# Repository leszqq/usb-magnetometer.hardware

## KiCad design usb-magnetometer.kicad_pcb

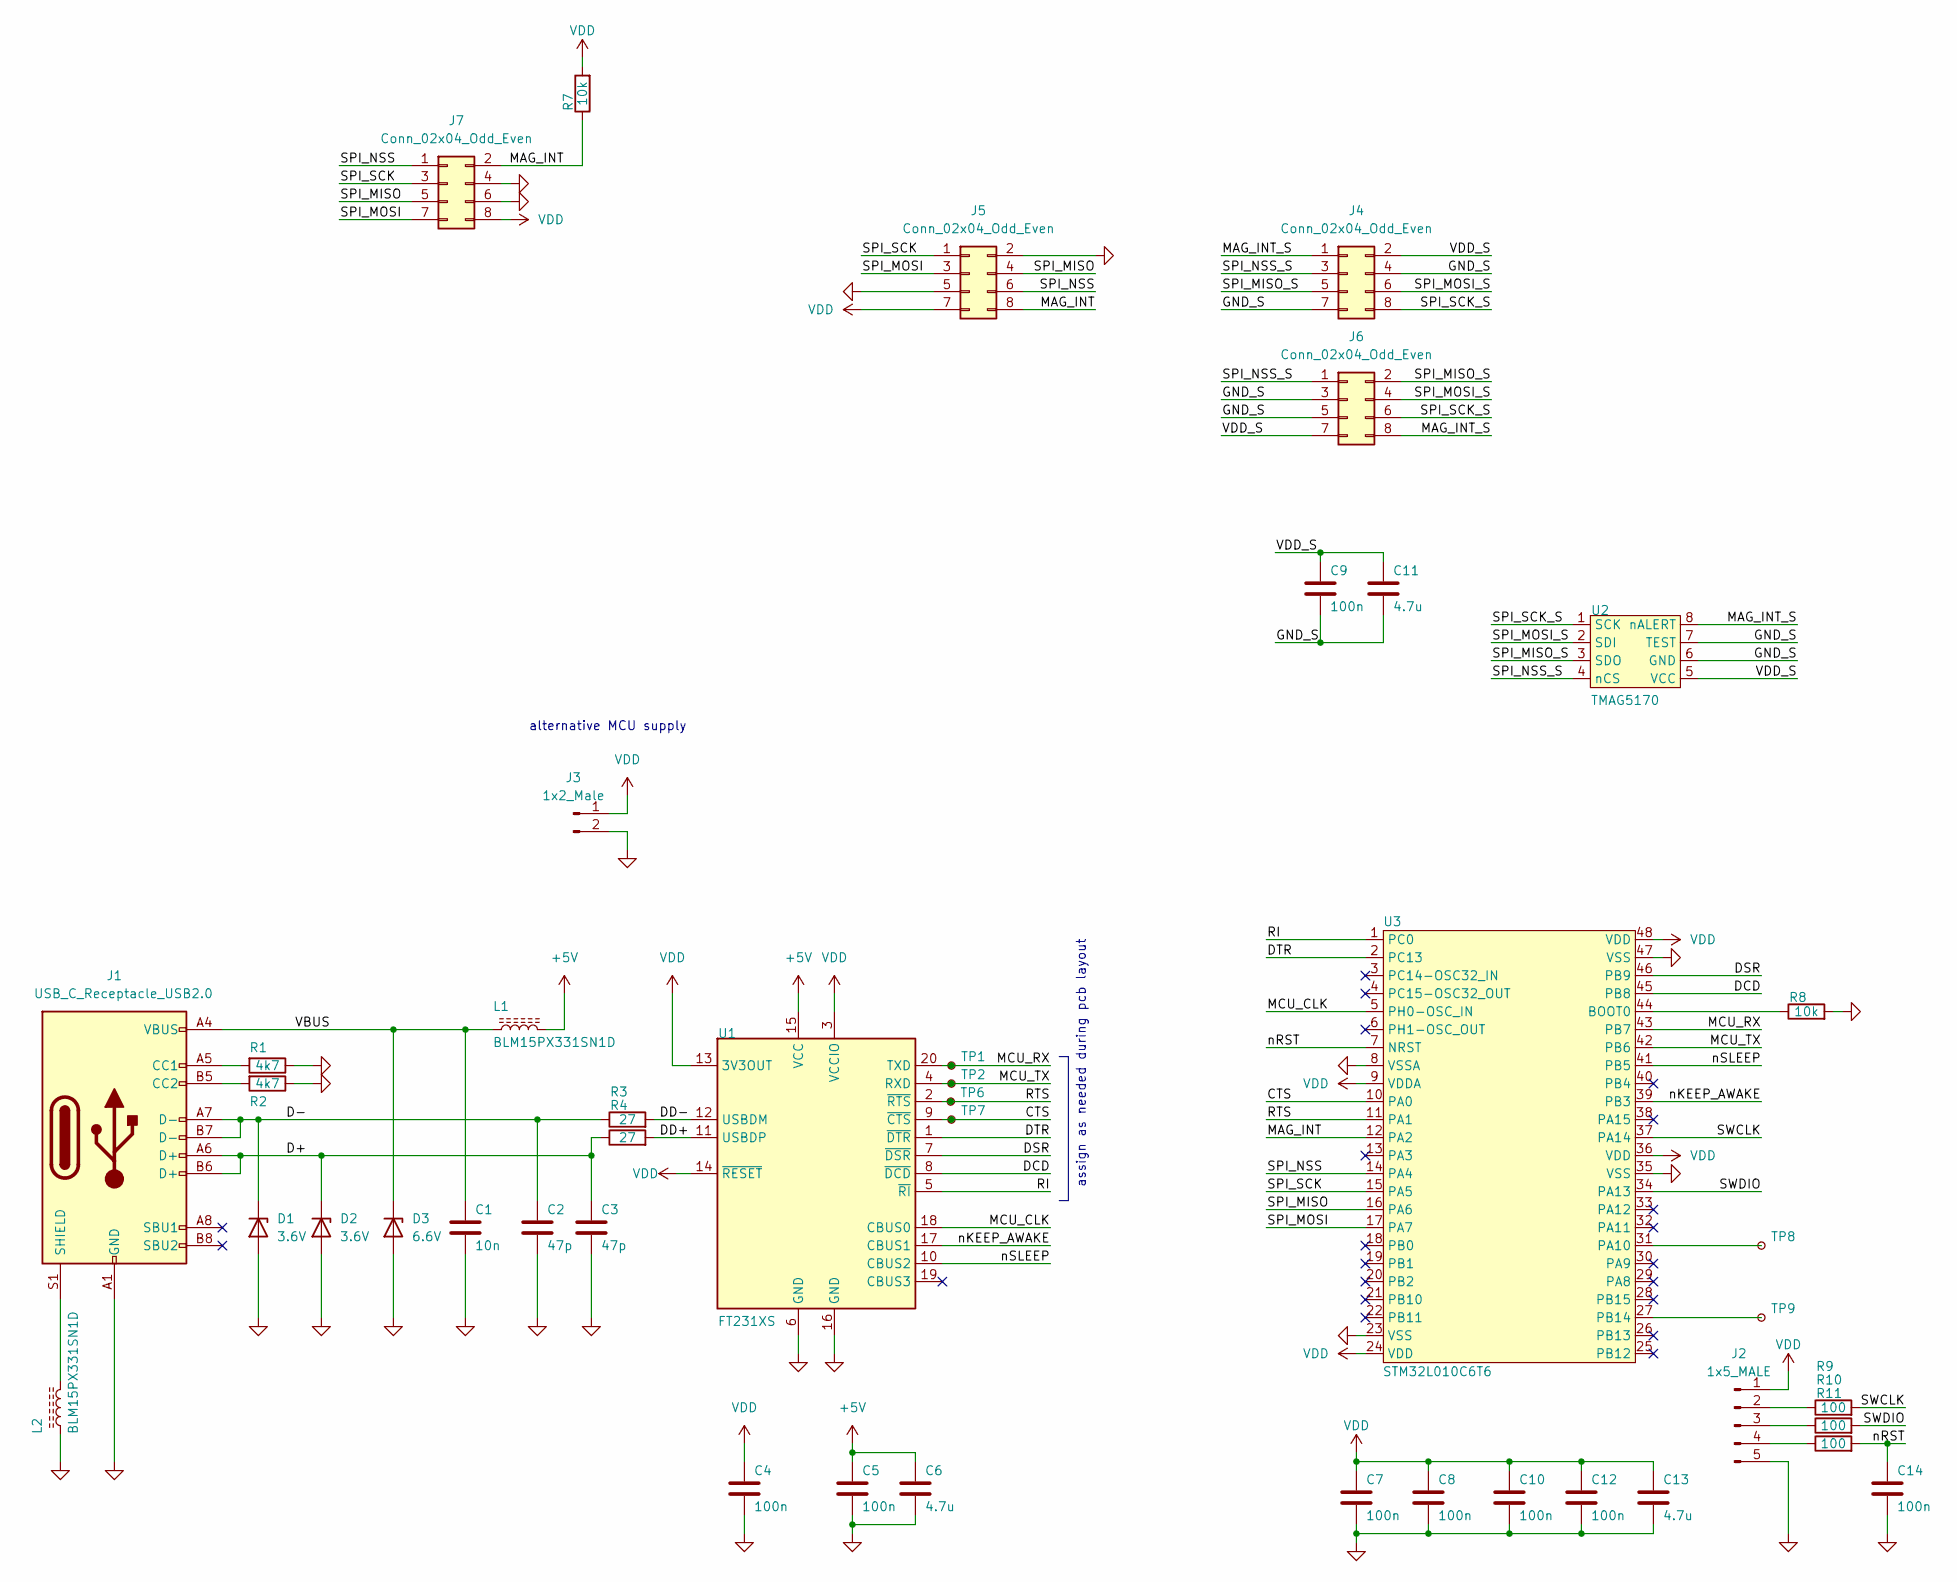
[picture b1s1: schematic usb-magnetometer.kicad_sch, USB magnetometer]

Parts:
C1: 10n; C_0402_1005Metric_Pad0.74x0.62mm_HandSolder; MPN VJ0402Y103JXQCW1BC
C2, C3: 47p; C_0402_1005Metric_Pad0.74x0.62mm_HandSolder; MPN CC0402JRNPO8BN470
C4, C5, C7, C8, C9, C10, C12, C14: 100n; C_0402_1005Metric_Pad0.74x0.62mm_HandSolder; MPN CL05A104KP5NNNC
C6, C11, C13: 4.7u; C_0402_1005Metric_Pad0.74x0.62mm_HandSolder; MPN CL05A475MP5NRNC
D1, D2: 3.6V; X1SON; MPN ESD321DPYR
D3: 6.6V; D_SOD-323_HandSoldering; MPN ESD3Z5V0
J1: USB_C_Receptacle_USB2.0; USB_C_Receptacle_JAE_DX07S016JA1R1500; MPN DX07S016JA1R1500
J2: 1x5_MALE; PinHeader_1x05_P2.54mm_Vertical; MPN *
J3: 1x2_Male; PinHeader_1x02_P2.54mm_Vertical; MPN *
J4, J5: Conn_02x04_Odd_Even; Hirose_FH12-8S-0.5SH_1x08-1MP_P0.50mm_Horizontal
J6, J7: Conn_02x04_Odd_Even; PinHeader_2x04_P1.00mm_Vertical
L1, L2: L_Ferrite; R_0402_1005Metric_Pad0.72x0.64mm_HandSolder; MPN BLM15PX331SN1D
R1, R2: 4k7; R_0402_1005Metric_Pad0.72x0.64mm_HandSolder; MPN RC0402JR-134K7L
R3, R4: 27; R_0402_1005Metric_Pad0.72x0.64mm_HandSolder; MPN RC0402JR-0727RL
R7, R8: 10k; R_0402_1005Metric_Pad0.72x0.64mm_HandSolder; MPN RC0402FR-0710KL
R9, R10, R11: 100; R_0402_1005Metric_Pad0.72x0.64mm_HandSolder; MPN RC0402FR-07100R
TP1, TP2, TP6, TP7, TP8, TP9: TestPoint_Small; TestPoint_Pad_D1.0mm
U1: FT231XS; SSOP-20_3.9x8.7mm_P0.635mm; MPN FT231XS-R
U2: TMAG5170; VSSOP-8_3.0x3.0mm_P0.65mm; MPN TMAG5170A1EDGKRQ1
U3: STM32L010C6T6; LQFP-48_7x7mm_P0.5mm; MPN STM32L010C6T6

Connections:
+5V: C5.1, C6.1, L1.2, U1.15 (VCC)
/CTS: TP7.1, U1.9 (~CTS), U3.10 (PA0)
/D+: C3.1, D2.1 (K), J1.A6 (D+), J1.B6 (D+), R4.1
/D-: C2.1, D1.1 (K), J1.A7 (D-), J1.B7 (D-), R3.1
/DCD: U1.8 (~DCD), U3.45 (PB8)
/DD+: R4.2, U1.11 (USBDP)
/DD-: R3.2, U1.12 (USBDM)
/DSR: U1.7 (~DSR), U3.46 (PB9)
/DTR: U1.1 (~DTR), U3.2 (PC13)
/GND_S: C9.2, C11.2, J4.4, J4.7, J6.3, J6.5, U2.6 (GND), U2.7 (TEST)
/MAG_INT: J5.8, J7.2, R7.1, U3.12 (PA2)
/MAG_INT_S: J4.1, J6.8, U2.8 (nALERT)
/MCU_CLK: U1.18 (CBUS0), U3.5 (PH0-OSC_IN)
/MCU_RX: TP1.1, U1.20 (TXD), U3.43 (PB7)
/MCU_TX: TP2.1, U1.4 (RXD), U3.42 (PB6)
/RI: U1.5 (~RI), U3.1 (PC0)
/RTS: TP6.1, U1.2 (~RTS), U3.11 (PA1)
/SPI_MISO: J5.4, J7.5, U3.16 (PA6)
/SPI_MISO_S: J4.5, J6.2, U2.3 (SDO)
/SPI_MOSI: J5.3, J7.7, U3.17 (PA7)
/SPI_MOSI_S: J4.6, J6.4, U2.2 (SDI)
/SPI_NSS: J5.6, J7.1, U3.14 (PA4)
/SPI_NSS_S: J4.3, J6.1, U2.4 (nCS)
/SPI_SCK: J5.1, J7.3, U3.15 (PA5)
/SPI_SCK_S: J4.8, J6.6, U2.1 (SCK)
/SWCLK: R9.2, U3.37 (PA14)
/SWDIO: R10.2, U3.34 (PA13)
/VBUS: C1.1, D3.1 (K), J1.A4 (VBUS), J1.A9 (VBUS), J1.B4 (VBUS), J1.B9 (VBUS), L1.1
/VDD_S: C9.1, C11.1, J4.2, J6.7, U2.5 (VCC)
/nKEEP_AWAKE: U1.17 (CBUS1), U3.39 (PB3)
/nRST: C14.1, R11.2, U3.7 (NRST)
/nSLEEP: U1.10 (CBUS2), U3.41 (PB5)
GND: C1.2, C2.2, C3.2, C4.2, C5.2, C6.2, C7.2, C8.2, C10.2, C12.2, C13.2, C14.2, D1.2 (A), D2.2 (A), D3.2 (A), J1.A1 (GND), J1.A12 (GND), J1.B1 (GND), J1.B12 (GND), J2.5, J3.2, J5.2, J5.5, J7.4, J7.6, L2.1, R1.1, R2.1, R8.2, U1.6 (GND), U1.16 (GND), U3.8 (VSSA), U3.23 (VSS), U3.35 (VSS), U3.47 (VSS)
unnamed: J1.A5 (CC1), R1.2
unnamed: J1.B5 (CC2), R2.2
unnamed: J1.S1 (SHIELD), L2.2
unnamed: J2.2, R9.1
unnamed: J2.3, R10.1
unnamed: J2.4, R11.1
unnamed: R8.1, U3.44 (BOOT0)
unnamed: TP8.1, U3.31 (PA10)
unnamed: TP9.1, U3.27 (PB14)
VDD: C4.1, C7.1, C8.1, C10.1, C12.1, C13.1, J2.1, J3.1, J5.7, J7.8, R7.2, U1.3 (VCCIO), U1.13 (3V3OUT), U1.14 (~RESET), U3.9 (VDDA), U3.24 (VDD), U3.36 (VDD), U3.48 (VDD)

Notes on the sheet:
assign as needed during pcb layout
alternative MCU supply

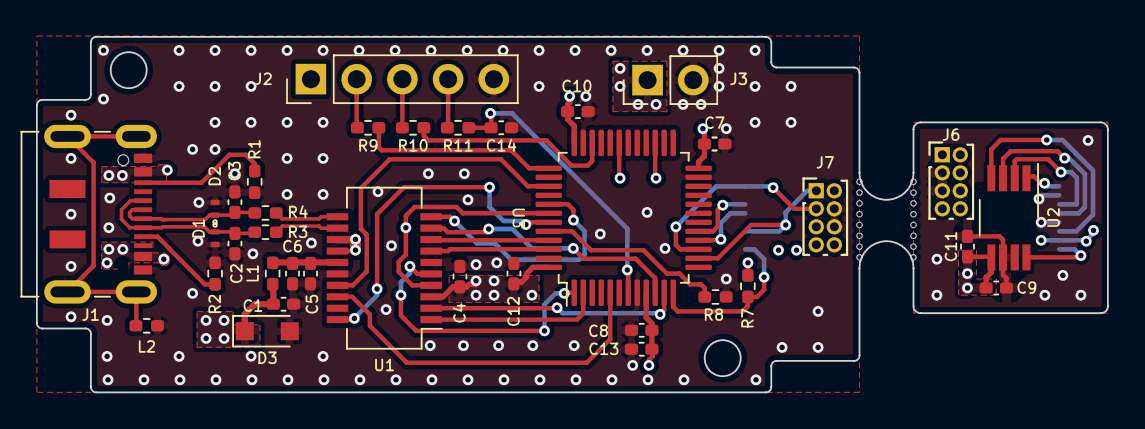
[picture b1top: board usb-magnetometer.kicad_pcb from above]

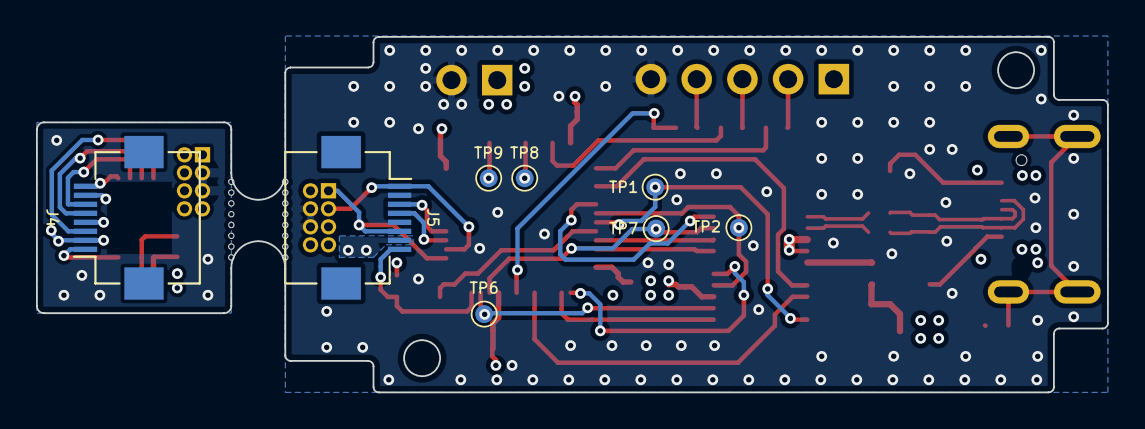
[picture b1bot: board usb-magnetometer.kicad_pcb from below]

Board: 4 copper layers, 59.5 x 19.8 mm, 44 parts (8 on the bottom side), 43 nets.

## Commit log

2023-02-05 Add v1.0 files
2023-03-12 Add initial version of separated pcbs
2023-03-14 Update conenctors designators size
2023-03-18 FPC connectors in progress
2023-03-18 Add final version with sensor on separated pcb
2023-03-18 Add fabrication outputs
2023-03-18 Make two pcb as one design
2023-04-02 Update ibom
